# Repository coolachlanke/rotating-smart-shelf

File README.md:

# Rotating Smart Shelf

Motorised display shelf for Rubik’s Cubes and other collectibles, powered by ESP32-C3 and WS2812B RGB LEDs.  
Designed for showpieces, timed rotations and eye-catching animations.

---

## 🧰 Tech Stack

- **Microcontroller:** ESP32-C3 (BLE, WiFi)
- **PCBs:** Custom power distrubution/driver/logic board + annular 48-pixel WS21812B carrier board. All designed in KiCAD 8.
- **Motors:** NEMA17 bipolar stepper motors with A4988 drivers
- **Power:** 9V barrel input with onboard 5V & 3V3 voltage regulation
- **Firmware:** Custom C++ firmware utiliting FreeRTOS built with PlatformIO (Arduino framework)
- **Lighting:** WS2812B addressable RGB LED rings for reactive effects
- **Control App:** Web-app interface for wireless control and presets
- **Features:**
  - Smooth timed rotation of platforms
  - Colour animations, brightness modulation, visual syncing
  - [UNDER CONSTRUCTION] Optional music-reactive visuals (via onboard mic or wireless data stream)

---

> Designed by Lachlan Cooke in late 2024.
> Check out [lachlancooke.com/projects](https://www.lachlancooke.com/projects) für mehr details.

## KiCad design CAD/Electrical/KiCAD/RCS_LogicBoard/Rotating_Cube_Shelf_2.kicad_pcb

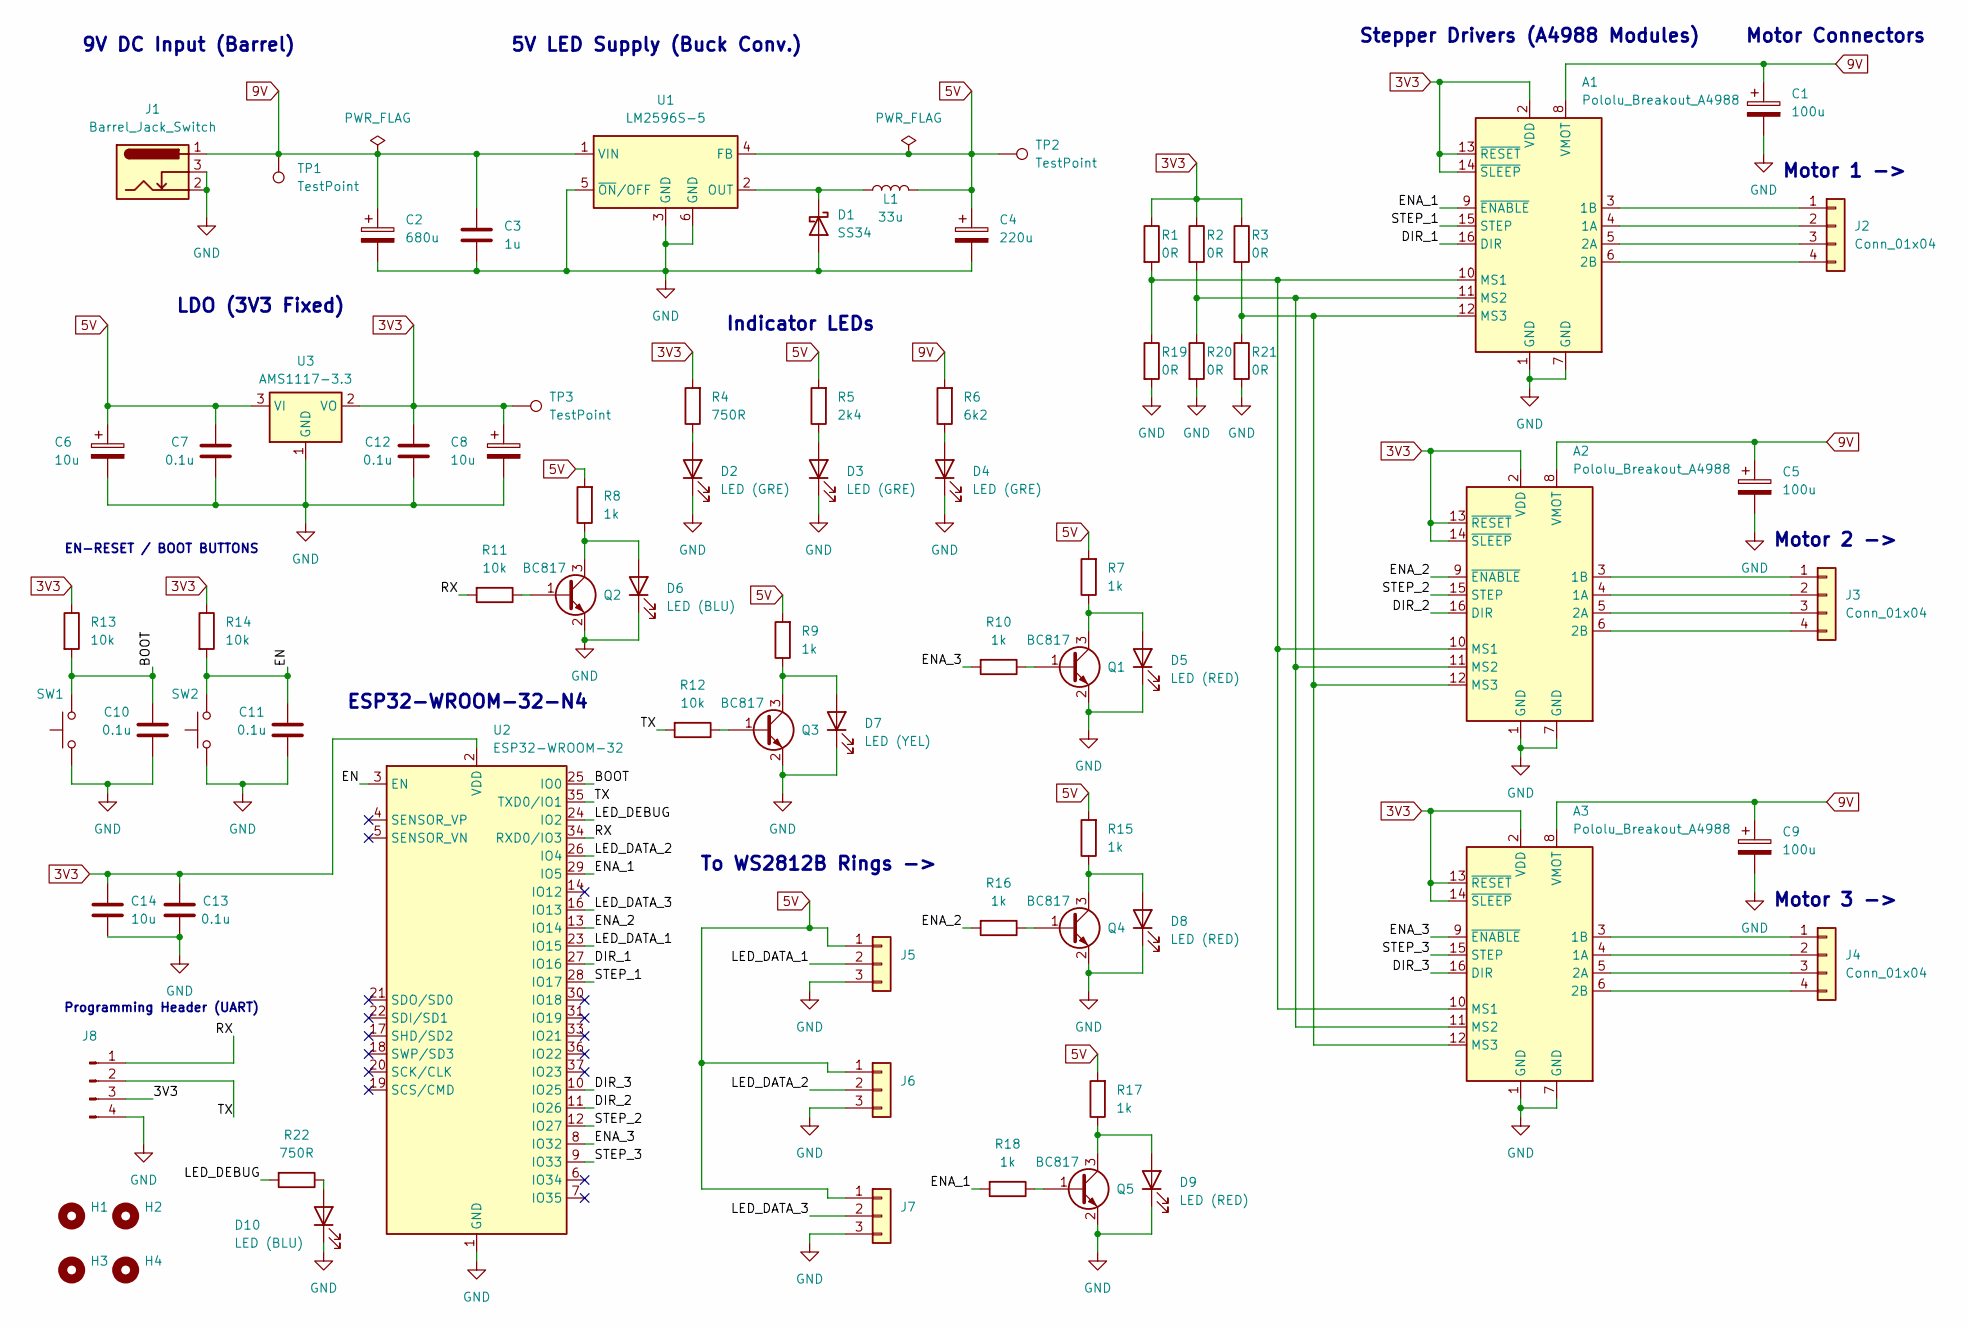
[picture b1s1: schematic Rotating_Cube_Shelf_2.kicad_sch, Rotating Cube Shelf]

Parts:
A1, A2, A3: Pololu_Breakout_A4988; Pololu_Breakout-16_15.2x20.3mm
C1, C5, C9: 100u; CP_Elec_8x10; LCSC C116241
C2: 680u; CP_Elec_10x10; LCSC C340751
C3: 1u; C_1206_3216Metric
C4: 220u; CP_Elec_10x10; LCSC C125977
C6, C8: 10u; CP_Elec_5x5.4; LCSC C4747971
C7, C12: 0.1u; C_0805_2012Metric
C10, C11, C13: 0.1u; C_0603_1608Metric
C14: 10u; C_0603_1608Metric
D1: SS34; D_SMA
D2, D3, D4: LED (GRE); D_0805_2012Metric; LCSC C965815
D5, D8, D9: LED (RED); D_0805_2012Metric; LCSC C965812
D6, D10: LED (BLU); D_0805_2012Metric; LCSC C965817
D7: LED (YEL); D_0805_2012Metric; LCSC C965814
H1, H2, H3, H4: MountingHole; MountingHole_3.2mm_M3
J1: Barrel_Jack_Switch; BarrelJack_Horizontal; LCSC C136744
J2, J3, J4: Conn_01x04; JST_XH_S4B-XH-A_1x04_P2.50mm_Horizontal; LCSC C157925
J5, J6, J7: Conn_01x03; JST_XH_B3B-XH-A_1x03_P2.50mm_Vertical; LCSC C161870
J8: Conn_01x04_Pin; PinHeader_1x04_P2.54mm_Vertical; LCSC C2691448
L1: 33u; SMDRI127; LCSC C9400
Q1, Q2, Q3, Q4, Q5: BC817; SOT-23; LCSC C52801
R1, R2, R3, R19, R20, R21: 0R; R_0603_1608Metric
R4, R22: 750R; R_0603_1608Metric
R5: 2k4; R_0603_1608Metric
R6: 6k2; R_0603_1608Metric
R7, R8, R9, R10, R15, R16, R17, R18: 1k; R_0603_1608Metric
R11, R12, R13, R14: 10k; R_0603_1608Metric
SW1, SW2: SW_Push; SW_PUSH_4.5mm; LCSC C455243
TP1, TP2, TP3: TestPoint; TestPoint_THTPad_D1.0mm_Drill0.5mm
U1: LM2596S-5; VREG_LM2596SX-5.0_NOPB
U2: ESP32-WROOM-32; LCSC C82899
U3: AMS1117-3.3; SOT-223-3_TabPin2; LCSC C6186

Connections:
3V3: A1.2 (VDD), A1.13 (~RESET), A1.14 (~SLEEP), A2.2 (VDD), A2.13 (~RESET), A2.14 (~SLEEP), A3.2 (VDD), A3.13 (~RESET), A3.14 (~SLEEP), C8.1, C12.2, C13.2, C14.2, J8.3, R1.1, R2.1, R3.1, R4.2, R13.1, R14.1, TP3.1, U2.2 (VDD), U3.2 (VO)
5V: C4.1, C6.1, C7.2, J5.1, J6.1, J7.1, L1.2, R5.2, R7.2, R8.2, R9.2, R15.2, R17.2, TP2.1, U1.4 (FB), U3.3 (VI)
9V: A1.8 (VMOT), A2.8 (VMOT), A3.8 (VMOT), C1.1, C2.1, C3.2, C5.1, C9.1, J1.1, R6.2, TP1.1, U1.1 (VIN)
/BOOT: C10.2, R13.2, SW1.2, U2.25 (IO0)
/DIR_1: A1.16 (DIR), U2.27 (IO16)
/DIR_2: A2.16 (DIR), U2.11 (IO26)
/DIR_3: A3.16 (DIR), U2.10 (IO25)
/EN: C11.2, R14.2, SW2.2, U2.3 (EN)
/ENA_1: A1.9 (~ENABLE), R18.2, U2.29 (IO5)
/ENA_2: A2.9 (~ENABLE), R16.2, U2.13 (IO14)
/ENA_3: A3.9 (~ENABLE), R10.2, U2.8 (IO32)
/LED_DATA_1: J5.2, U2.23 (IO15)
/LED_DATA_2: J6.2, U2.26 (IO4)
/LED_DATA_3: J7.2, U2.16 (IO13)
/LED_DEBUG: R22.2, U2.24 (IO2)
/RX: J8.1, R11.2, U2.34 (RXD0/IO3)
/STEP_1: A1.15 (STEP), U2.28 (IO17)
/STEP_2: A2.15 (STEP), U2.12 (IO27)
/STEP_3: A3.15 (STEP), U2.9 (IO33)
/TX: J8.2, R12.2, U2.35 (TXD0/IO1)
GND: A1.1 (GND), A1.7 (GND), A2.1 (GND), A2.7 (GND), A3.1 (GND), A3.7 (GND), C1.2, C2.2, C3.1, C4.2, C5.2, C6.2, C7.1, C8.2, C9.2, C10.1, C11.1, C12.1, C13.1, C14.1, D1.2 (A), D2.1 (K), D3.1 (K), D4.1 (K), D5.1 (K), D6.1 (K), D7.1 (K), D8.1 (K), D9.1 (K), D10.1 (K), J1.2, J1.3, J5.3, J6.3, J7.3, J8.4, Q1.2 (E), Q2.2 (E), Q3.2 (E), Q4.2 (E), Q5.2 (E), R19.2, R20.2, R21.2, SW1.1, SW2.1, U1.3 (GND), U1.5 (~ON/OFF), U1.6 (GND), U2.1 (GND), U2.15 (GND), U2.38 (GND), U2.39 (GND), U3.1 (GND)
unnamed: A1.4 (1A), J2.2
unnamed: A1.3 (1B), J2.1
unnamed: A1.5 (2A), J2.3
unnamed: A1.6 (2B), J2.4
unnamed: A1.10 (MS1), A2.10 (MS1), A3.10 (MS1), R1.2, R19.1
unnamed: A1.11 (MS2), A2.11 (MS2), A3.11 (MS2), R2.2, R20.1
unnamed: A1.12 (MS3), A2.12 (MS3), A3.12 (MS3), R3.2, R21.1
unnamed: A2.4 (1A), J3.2
unnamed: A2.3 (1B), J3.1
unnamed: A2.5 (2A), J3.3
unnamed: A2.6 (2B), J3.4
unnamed: A3.4 (1A), J4.2
unnamed: A3.3 (1B), J4.1
unnamed: A3.5 (2A), J4.3
unnamed: A3.6 (2B), J4.4
unnamed: D1.1 (K), L1.1, U1.2 (OUT)
unnamed: D2.2 (A), R4.1
unnamed: D3.2 (A), R5.1
unnamed: D4.2 (A), R6.1
unnamed: D5.2 (A), Q1.3 (C), R7.1
unnamed: D6.2 (A), Q2.3 (C), R8.1
unnamed: D7.2 (A), Q3.3 (C), R9.1
unnamed: D8.2 (A), Q4.3 (C), R15.1
unnamed: D9.2 (A), Q5.3 (C), R17.1
unnamed: D10.2 (A), R22.1
unnamed: Q1.1 (B), R10.1
unnamed: Q2.1 (B), R11.1
unnamed: Q3.1 (B), R12.1
unnamed: Q4.1 (B), R16.1
unnamed: Q5.1 (B), R18.1

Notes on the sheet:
Stepper Drivers (A4988 Modules)
5V LED Supply (Buck Conv.)
EN-RESET / BOOT BUTTONS
To WS2812B Rings ->
Motor 3 ->
9V DC Input (Barrel)
Motor Connectors
Programming Header (UART)
Indicator LEDs
ESP32-WROOM-32-N4
Motor 1 ->
LDO (3V3 Fixed)
Motor 2 ->

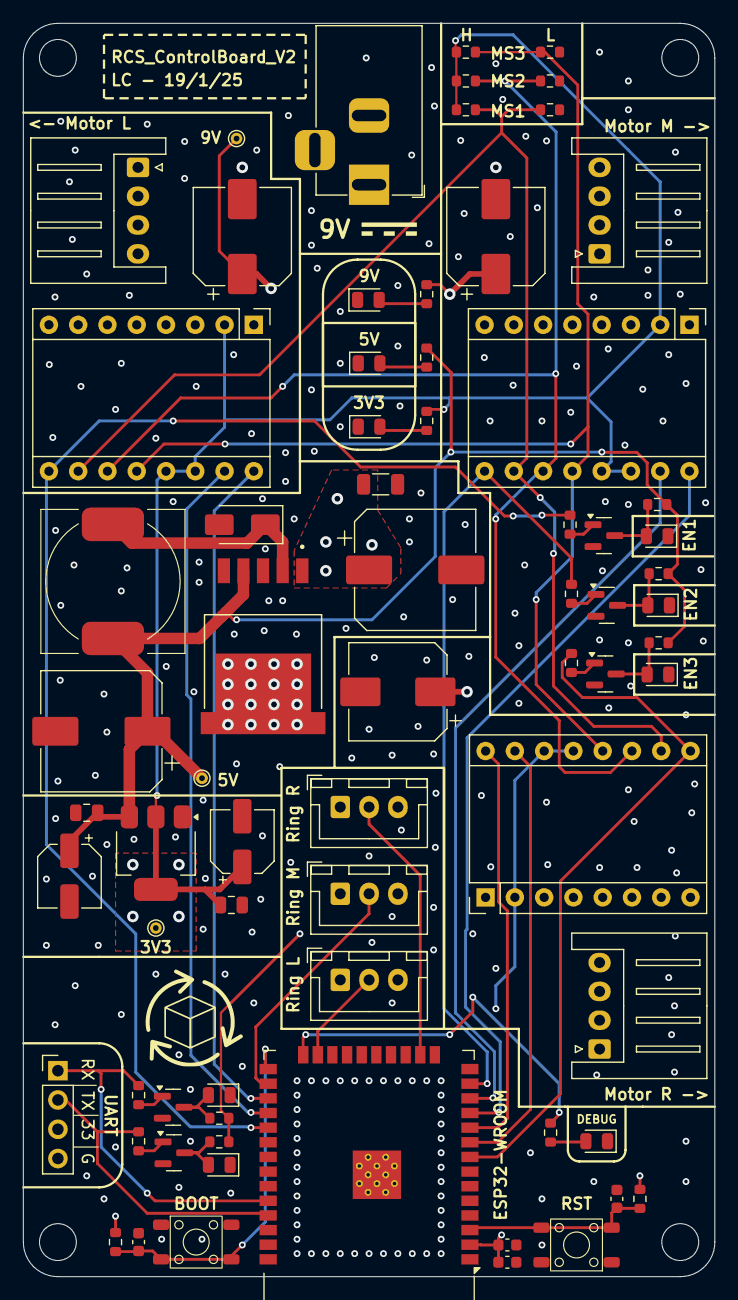
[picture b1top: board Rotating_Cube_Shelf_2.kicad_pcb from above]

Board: 4 copper layers, 60.0 x 108.8 mm, 75 parts (0 on the bottom side), 51 nets.

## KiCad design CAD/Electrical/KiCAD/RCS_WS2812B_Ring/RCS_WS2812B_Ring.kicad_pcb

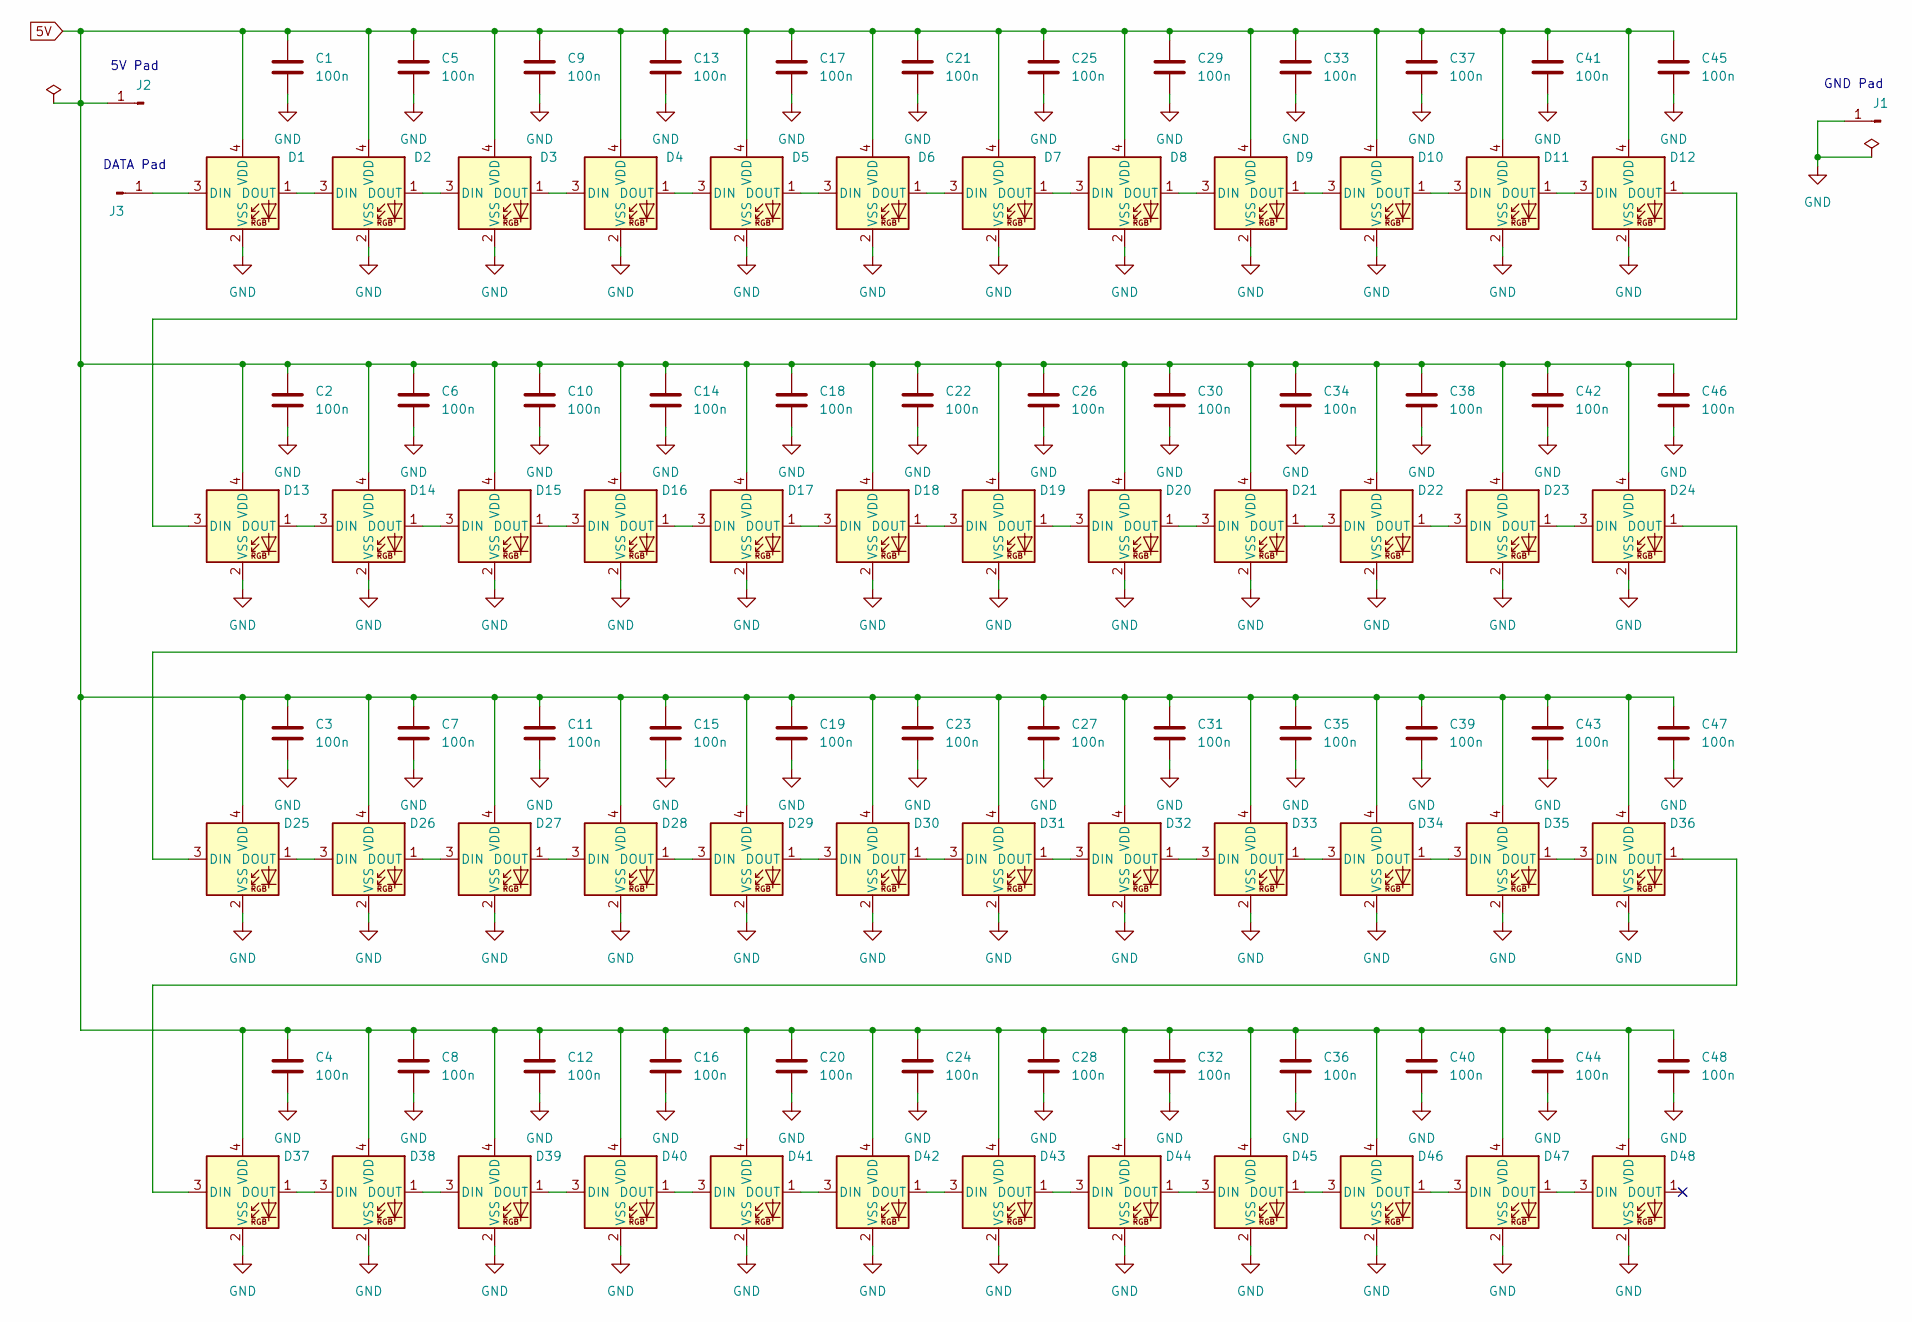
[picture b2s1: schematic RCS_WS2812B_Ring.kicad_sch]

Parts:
C1, C2, C3, C4, C5, C6, C7, C8, C9, C10, C11, C12, C13, C14, C15, C16, C17, C18, C19, C20, C21, C22, C23, C24, C25, C26, C27, C28, C29, C30, C31, C32, C33, C34, C35, C36, C37, C38, C39, C40, C41, C42, C43, C44, C45, C46, C47, C48: 100n; C_0603_1608Metric
D1, D2, D3, D4, D5, D6, D7, D8, D9, D10, D11, D12, D13, D14, D15, D16, D17, D18, D19, D20, D21, D22, D23, D24, D25, D26, D27, D28, D29, D30, D31, D32, D33, D34, D35, D36, D37, D38, D39, D40, D41, D42, D43, D44, D45, D46, D47, D48: WS2812B-2020; LED_WS2812B-2020_PLCC4_2.0x2.0mm
J1, J2, J3: Conn_01x01_Pin; PAD_WS2812B_RING

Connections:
5V: C1.1, C2.1, C3.1, C4.1, C5.1, C6.1, C7.1, C8.1, C9.1, C10.1, C11.1, C12.1, C13.1, C14.1, C15.1, C16.1, C17.1, C18.1, C19.1, C20.1, C21.1, C22.1, C23.1, C24.1, C25.1, C26.1, C27.1, C28.1, C29.1, C30.1, C31.1, C32.1, C33.1, C34.1, C35.1, C36.1, C37.1, C38.1, C39.1, C40.1, C41.1, C42.1, C43.1, C44.1, C45.1, C46.1, C47.1, C48.1, D1.4 (VDD), D2.4 (VDD), D3.4 (VDD), D4.4 (VDD), D5.4 (VDD), D6.4 (VDD), D7.4 (VDD), D8.4 (VDD), D9.4 (VDD), D10.4 (VDD), D11.4 (VDD), D12.4 (VDD), D13.4 (VDD), D14.4 (VDD), D15.4 (VDD), D16.4 (VDD), D17.4 (VDD), D18.4 (VDD), D19.4 (VDD), D20.4 (VDD), D21.4 (VDD), D22.4 (VDD), D23.4 (VDD), D24.4 (VDD), D25.4 (VDD), D26.4 (VDD), D27.4 (VDD), D28.4 (VDD), D29.4 (VDD), D30.4 (VDD), D31.4 (VDD), D32.4 (VDD), D33.4 (VDD), D34.4 (VDD), D35.4 (VDD), D36.4 (VDD), D37.4 (VDD), D38.4 (VDD), D39.4 (VDD), D40.4 (VDD), D41.4 (VDD), D42.4 (VDD), D43.4 (VDD), D44.4 (VDD), D45.4 (VDD), D46.4 (VDD), D47.4 (VDD), D48.4 (VDD), J2.1
GND: C1.2, C2.2, C3.2, C4.2, C5.2, C6.2, C7.2, C8.2, C9.2, C10.2, C11.2, C12.2, C13.2, C14.2, C15.2, C16.2, C17.2, C18.2, C19.2, C20.2, C21.2, C22.2, C23.2, C24.2, C25.2, C26.2, C27.2, C28.2, C29.2, C30.2, C31.2, C32.2, C33.2, C34.2, C35.2, C36.2, C37.2, C38.2, C39.2, C40.2, C41.2, C42.2, C43.2, C44.2, C45.2, C46.2, C47.2, C48.2, D1.2 (VSS), D2.2 (VSS), D3.2 (VSS), D4.2 (VSS), D5.2 (VSS), D6.2 (VSS), D7.2 (VSS), D8.2 (VSS), D9.2 (VSS), D10.2 (VSS), D11.2 (VSS), D12.2 (VSS), D13.2 (VSS), D14.2 (VSS), D15.2 (VSS), D16.2 (VSS), D17.2 (VSS), D18.2 (VSS), D19.2 (VSS), D20.2 (VSS), D21.2 (VSS), D22.2 (VSS), D23.2 (VSS), D24.2 (VSS), D25.2 (VSS), D26.2 (VSS), D27.2 (VSS), D28.2 (VSS), D29.2 (VSS), D30.2 (VSS), D31.2 (VSS), D32.2 (VSS), D33.2 (VSS), D34.2 (VSS), D35.2 (VSS), D36.2 (VSS), D37.2 (VSS), D38.2 (VSS), D39.2 (VSS), D40.2 (VSS), D41.2 (VSS), D42.2 (VSS), D43.2 (VSS), D44.2 (VSS), D45.2 (VSS), D46.2 (VSS), D47.2 (VSS), D48.2 (VSS), J1.1
unnamed: D1.3 (DIN), J3.1
unnamed: D1.1 (DOUT), D2.3 (DIN)
unnamed: D2.1 (DOUT), D3.3 (DIN)
unnamed: D3.1 (DOUT), D4.3 (DIN)
unnamed: D4.1 (DOUT), D5.3 (DIN)
unnamed: D5.1 (DOUT), D6.3 (DIN)
unnamed: D6.1 (DOUT), D7.3 (DIN)
unnamed: D7.1 (DOUT), D8.3 (DIN)
unnamed: D8.1 (DOUT), D9.3 (DIN)
unnamed: D9.1 (DOUT), D10.3 (DIN)
unnamed: D10.1 (DOUT), D11.3 (DIN)
unnamed: D11.1 (DOUT), D12.3 (DIN)
unnamed: D12.1 (DOUT), D13.3 (DIN)
unnamed: D13.1 (DOUT), D14.3 (DIN)
unnamed: D14.1 (DOUT), D15.3 (DIN)
unnamed: D15.1 (DOUT), D16.3 (DIN)
unnamed: D16.1 (DOUT), D17.3 (DIN)
unnamed: D17.1 (DOUT), D18.3 (DIN)
unnamed: D18.1 (DOUT), D19.3 (DIN)
unnamed: D19.1 (DOUT), D20.3 (DIN)
unnamed: D20.1 (DOUT), D21.3 (DIN)
unnamed: D21.1 (DOUT), D22.3 (DIN)
unnamed: D22.1 (DOUT), D23.3 (DIN)
unnamed: D23.1 (DOUT), D24.3 (DIN)
unnamed: D24.1 (DOUT), D25.3 (DIN)
unnamed: D25.1 (DOUT), D26.3 (DIN)
unnamed: D26.1 (DOUT), D27.3 (DIN)
unnamed: D27.1 (DOUT), D28.3 (DIN)
unnamed: D28.1 (DOUT), D29.3 (DIN)
unnamed: D29.1 (DOUT), D30.3 (DIN)
unnamed: D30.1 (DOUT), D31.3 (DIN)
unnamed: D31.1 (DOUT), D32.3 (DIN)
unnamed: D32.1 (DOUT), D33.3 (DIN)
unnamed: D33.1 (DOUT), D34.3 (DIN)
unnamed: D34.1 (DOUT), D35.3 (DIN)
unnamed: D35.1 (DOUT), D36.3 (DIN)
unnamed: D36.1 (DOUT), D37.3 (DIN)
unnamed: D37.1 (DOUT), D38.3 (DIN)
unnamed: D38.1 (DOUT), D39.3 (DIN)
unnamed: D39.1 (DOUT), D40.3 (DIN)
unnamed: D40.1 (DOUT), D41.3 (DIN)
unnamed: D41.1 (DOUT), D42.3 (DIN)
unnamed: D42.1 (DOUT), D43.3 (DIN)
unnamed: D43.1 (DOUT), D44.3 (DIN)
unnamed: D44.1 (DOUT), D45.3 (DIN)
unnamed: D45.1 (DOUT), D46.3 (DIN)
unnamed: D46.1 (DOUT), D47.3 (DIN)
unnamed: D47.1 (DOUT), D48.3 (DIN)

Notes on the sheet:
GND Pad
5V Pad
DATA Pad

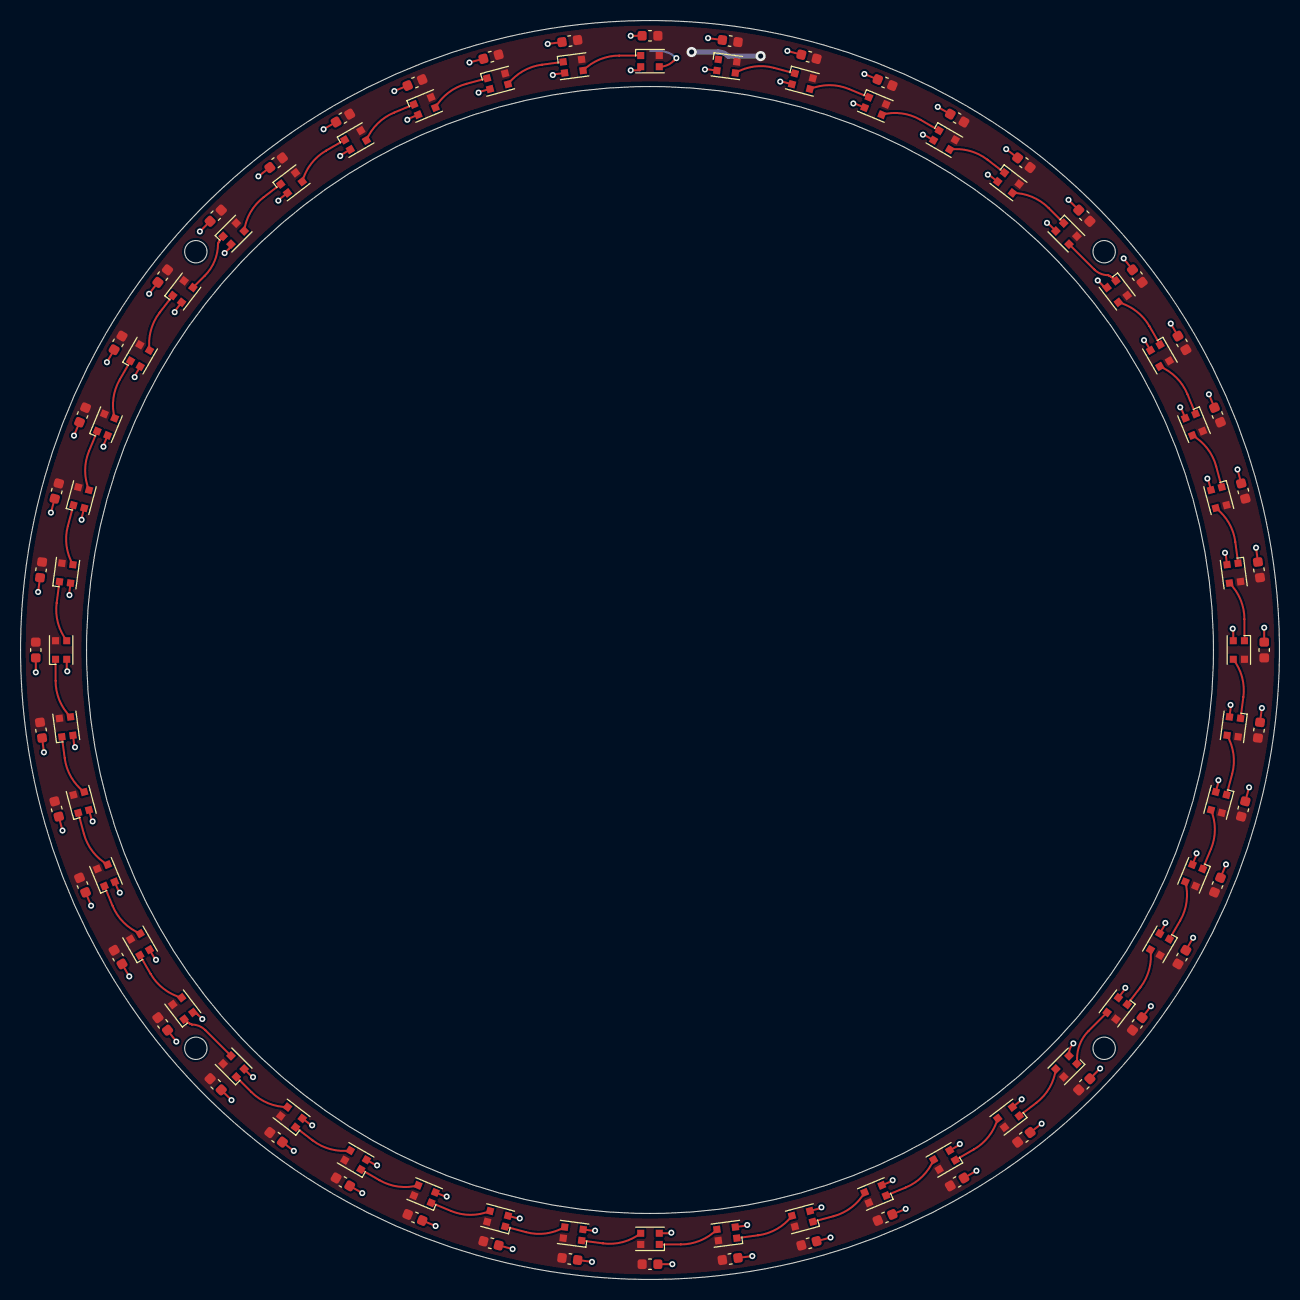
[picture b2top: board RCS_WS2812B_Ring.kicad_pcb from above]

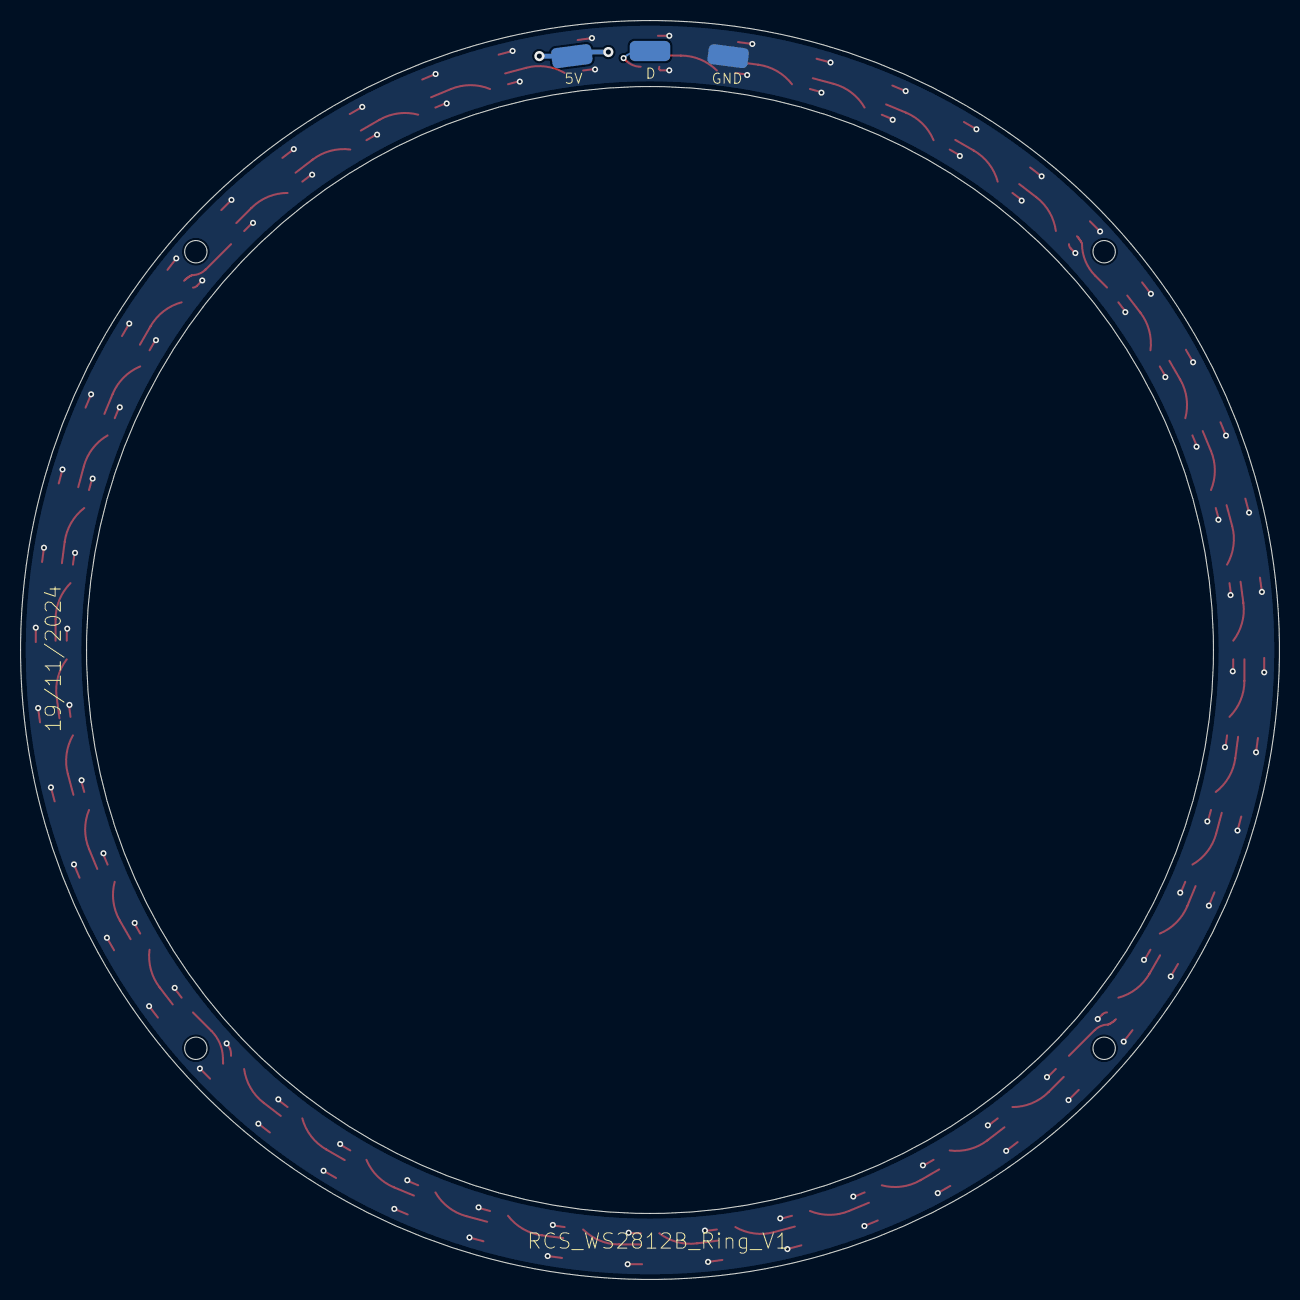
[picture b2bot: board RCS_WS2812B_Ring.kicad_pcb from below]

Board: 2 copper layers, 124.0 x 124.0 mm, 99 parts (3 on the bottom side), 50 nets.

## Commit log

2025-06-13 Initial commit - rotating cube shelf full project
2025-06-13 Create README.md oh yeah best part
2025-06-13 Update README.md oh yeahhhh
2025-06-13 Update README.md spelling - oh yeah VECTORRRR!!!
